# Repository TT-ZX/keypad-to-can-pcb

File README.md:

# keypad-to-can-pcb
PCB to interface a matrix keypad to a CAN bus.

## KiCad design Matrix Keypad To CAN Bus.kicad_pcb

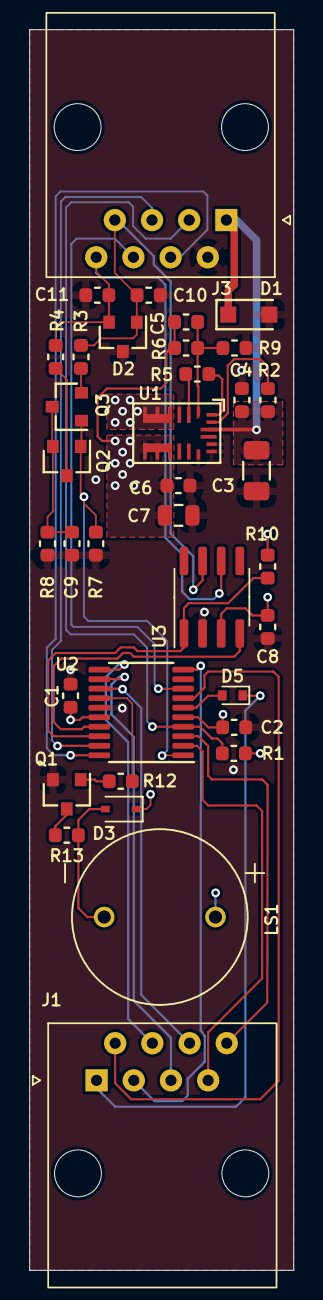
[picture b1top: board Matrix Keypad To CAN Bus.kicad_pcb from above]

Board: 4 copper layers, 18.0 x 84.7 mm, 36 parts (0 on the bottom side), 32 nets.

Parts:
C1, C2, C4, C6, C8: C0603C104K5RACTU; C_0603_1608Metric
C3: GRM319R6YA106KA12D; C_1206_3216Metric
C5: 06031A220KAT2A; C_0603_1608Metric
C7: CL21A226KPCLRNC; C_0805_2012Metric
C9, C10, C11: C-CER-0603-4.7PF-50V-1; C_0603_1608Metric
D1: PTVS24VS1UTR,115; D_SOD-123W
D2: AQ24CANFD-02HTG; SOT-23-3
D3: D-SCH-30V-800MA-SOD323-1; D_SOD-323
D5: D-SCH-30V-30MA-SOD523-1; D_SOD-523
J1, J3: J-RJ-RJ45-NOSHLD-THT-1; 54602-908LF
LS1: AI-1223-TWT-3V-2-R; XDCR_AI-1223-TWT-3V-2-R
Q1: Q-BJT-NPN-40V-600MA-SOT233-1; SOT-23-3
Q2, Q3: FDN352AP; SOT-23-3
R1, R5: RMCF0603FT10K0; R_0603_1608Metric
R2: RMCF0603FT100K; R_0603_1608Metric
R3, R4: R-0603-60R4-1P-1; R_0603_1608Metric
R6: RMCF0603FT160K; R_0603_1608Metric
R7: R-0603-33KR-1P-1; R_0603_1608Metric
R8: R-0603-100KR-1P-1; R_0603_1608Metric
R9: R-0603-51KR-1P-1; R_0603_1608Metric
R10: RMCF0603FT4K70; R_0603_1608Metric
R12: R-0603-1KR-1P-1; R_0603_1608Metric
R13: R-0603-10R-1P-1; R_0603_1608Metric
U1: MPM3620GQV-Z; QFN-20-MPM3620GQV-Z
U2: STM32F042F4P6TR; TSSOP-20_4.4x6.5mm_P0.65mm
U3: I-TXRX-CAN-1MB-SOIC8-2; SOIC-8_3.9x4.9mm_P1.27mm

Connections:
+3V3: C1.1, C2.1, C5.1, C6.1, C7.1, C8.1, D3.1 (K), LS1.P (p), R1.1, R6.1, R10.1, U1.7 (OUT), U1.8 (OUT), U1.9 (OUT), U2.5 (VDDA), U2.16 (VDD), U3.3 (Vcc)
+24V: C3.1, C4.1, D1.1 (A1), J3.1, R2.2, U1.16 (IN)
/BUZZER: R12.1, U2.14 (PB1)
/CAN_RES: Q2.1 (G), Q3.1 (G), R7.1, U2.1 (PB8)
/CAN_RX: U2.17 (PA9/PA11), U3.4 (RXD)
/CAN_TX: R10.2, U2.18 (PA10/PA12), U3.1 (TXD)
/K_1: J1.3, U2.10 (PA4)
/K_2: J1.4, U2.11 (PA5)
/K_3: J1.5, U2.12 (PA6)
/K_4: J1.6, U2.13 (PA7)
/K_A: D5.2 (A), U2.6 (PA0)
/K_B: J1.2, U2.7 (PA1)
/K_C: J1.8, U2.3 (PF1)
/K_D: J1.7, U2.2 (PF0)
/SWCLK_STM: J3.4, U2.20 (PA14)
/SWDIO_STM: J3.5, U2.19 (PA13)
/SWRST: J3.3, R1.2, U2.4 (NRST)
/USART2_TX: J3.6, U2.8 (PA2)
GND: C1.2, C2.2, C3.2, C4.2, C6.2, C7.2, C8.2, C9.2, C10.2, C11.2, D1.2 (A2), D2.3 (common), J3.2, Q1.2 (E), R7.2, R8.2, R9.2, U1.3 (AGND), U1.12 (PGND), U1.13 (PGND), U1.14 (PGND), U2.15 (VSS), U3.2 (GND)
unnamed: C10.1, D2.1 (A1), J3.7, R3.1, U3.7 (CANH)
unnamed: C11.1, D2.2 (A2), J3.8, R4.1, U3.6 (CANL)
unnamed: D3.2 (A), LS1.N (-), R13.1
unnamed: D5.1 (K), J1.1
unnamed: Q1.1 (B), R12.2
unnamed: Q1.3 (C), R13.2
unnamed: Q2.3 (D), R4.2
unnamed: C9.1, Q2.2 (S), Q3.3 (D), R8.1
unnamed: Q3.2 (S), R3.2
unnamed: R5.1, U1.18 (AAM)
unnamed: R2.1, U1.17 (EN/SYNC)
unnamed: C5.2, R6.2, R9.1, U1.1 (FB)
unnamed: R5.2, U1.2 (VCC)

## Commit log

2025-12-29 Version 2 files
